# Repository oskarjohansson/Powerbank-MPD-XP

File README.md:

# Powerbank 4S
A powerbank to primarily use with MDP-XP Modular Power Supply. It can be found [here](https://www.welectron.com/Miniware-MDP-XP-Modular-Power-Supply). 

## Background 
One of the problems when using li-ion batteries is the charging, without a proper charger the cells wil be damages and probably start a fire. To remove these problems one solution would be a BMS with USB-C as a charging and discharging port. This doesn't exist yet, so someone has to make it. 

## Specification
- 4S high power Li-ion 
- Charge with USB-C
- Discharge with USB-C/DC jack

## Hardware core

> The following parts will be used as the main part of the project

* Charge controller from TI - [BQ25723RSNR](https://www.ti.com/lit/ds/symlink/bq25723.pdf?ts=1637573546478&ref_url=https%253A%252F%252Feu.mouser.com%252F)
* USB-C PD Interface from onsemi - [FUSB302B01MPX](https://www.mouser.se/datasheet/2/308/1/FUSB302B_D-2314121.pdf)
* MCU from Microchip - [ATSAMD21G18A](https://ww1.microchip.com/downloads/en/DeviceDoc/SAM-D21DA1-Family-Data-Sheet-DS40001882G.pdf)

# Schematic and PCB

## PCB

* TBD

## Schematic 

* TBD

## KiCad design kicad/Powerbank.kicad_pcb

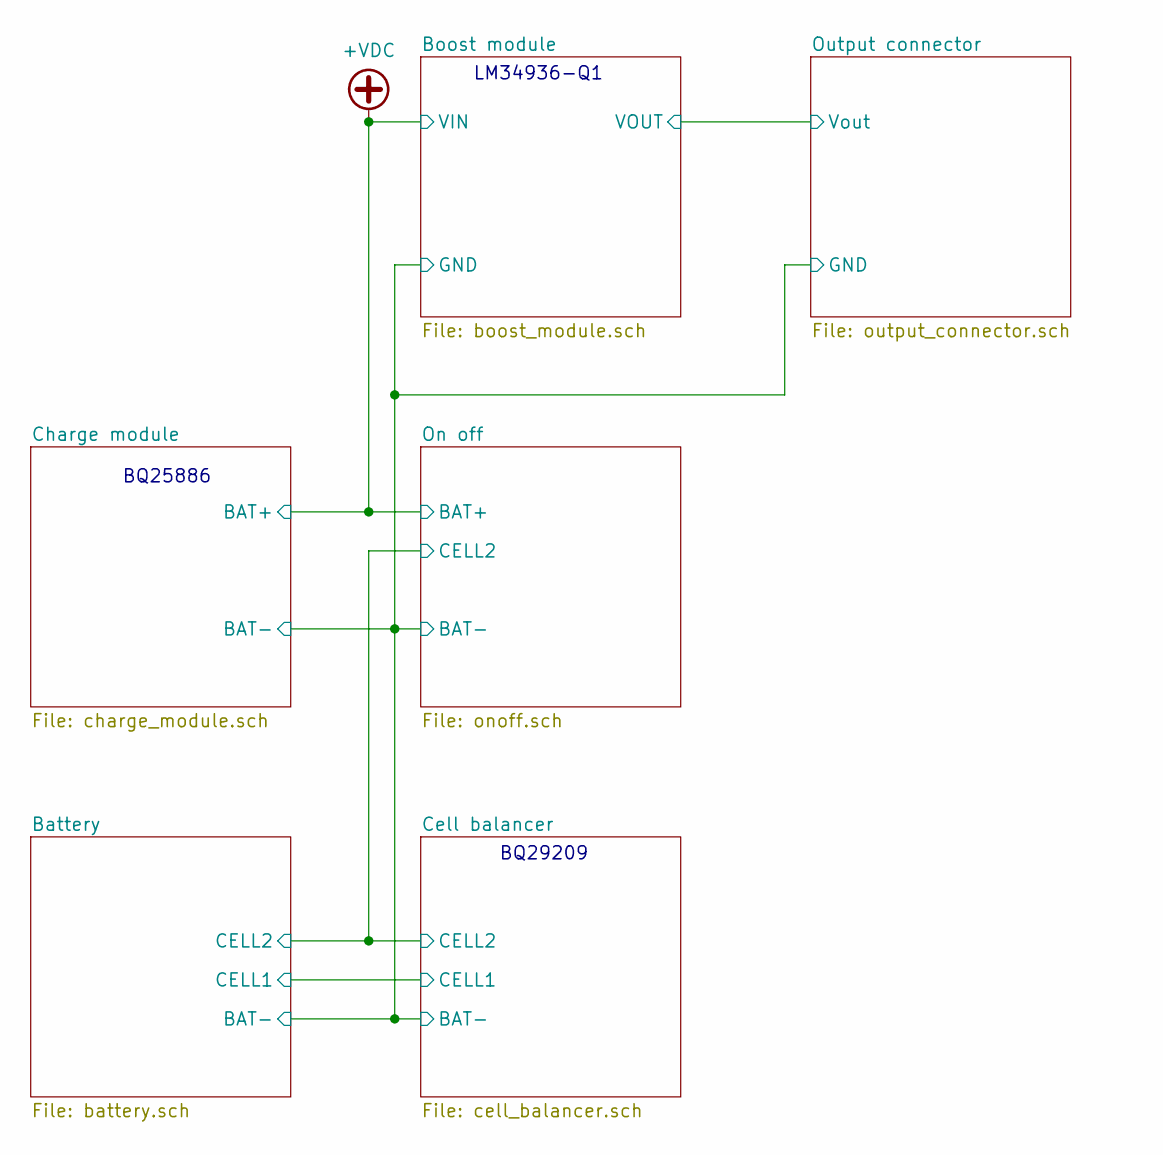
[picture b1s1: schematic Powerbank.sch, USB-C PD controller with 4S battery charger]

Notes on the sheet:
BQ25886
LM34936-Q1
BQ29209

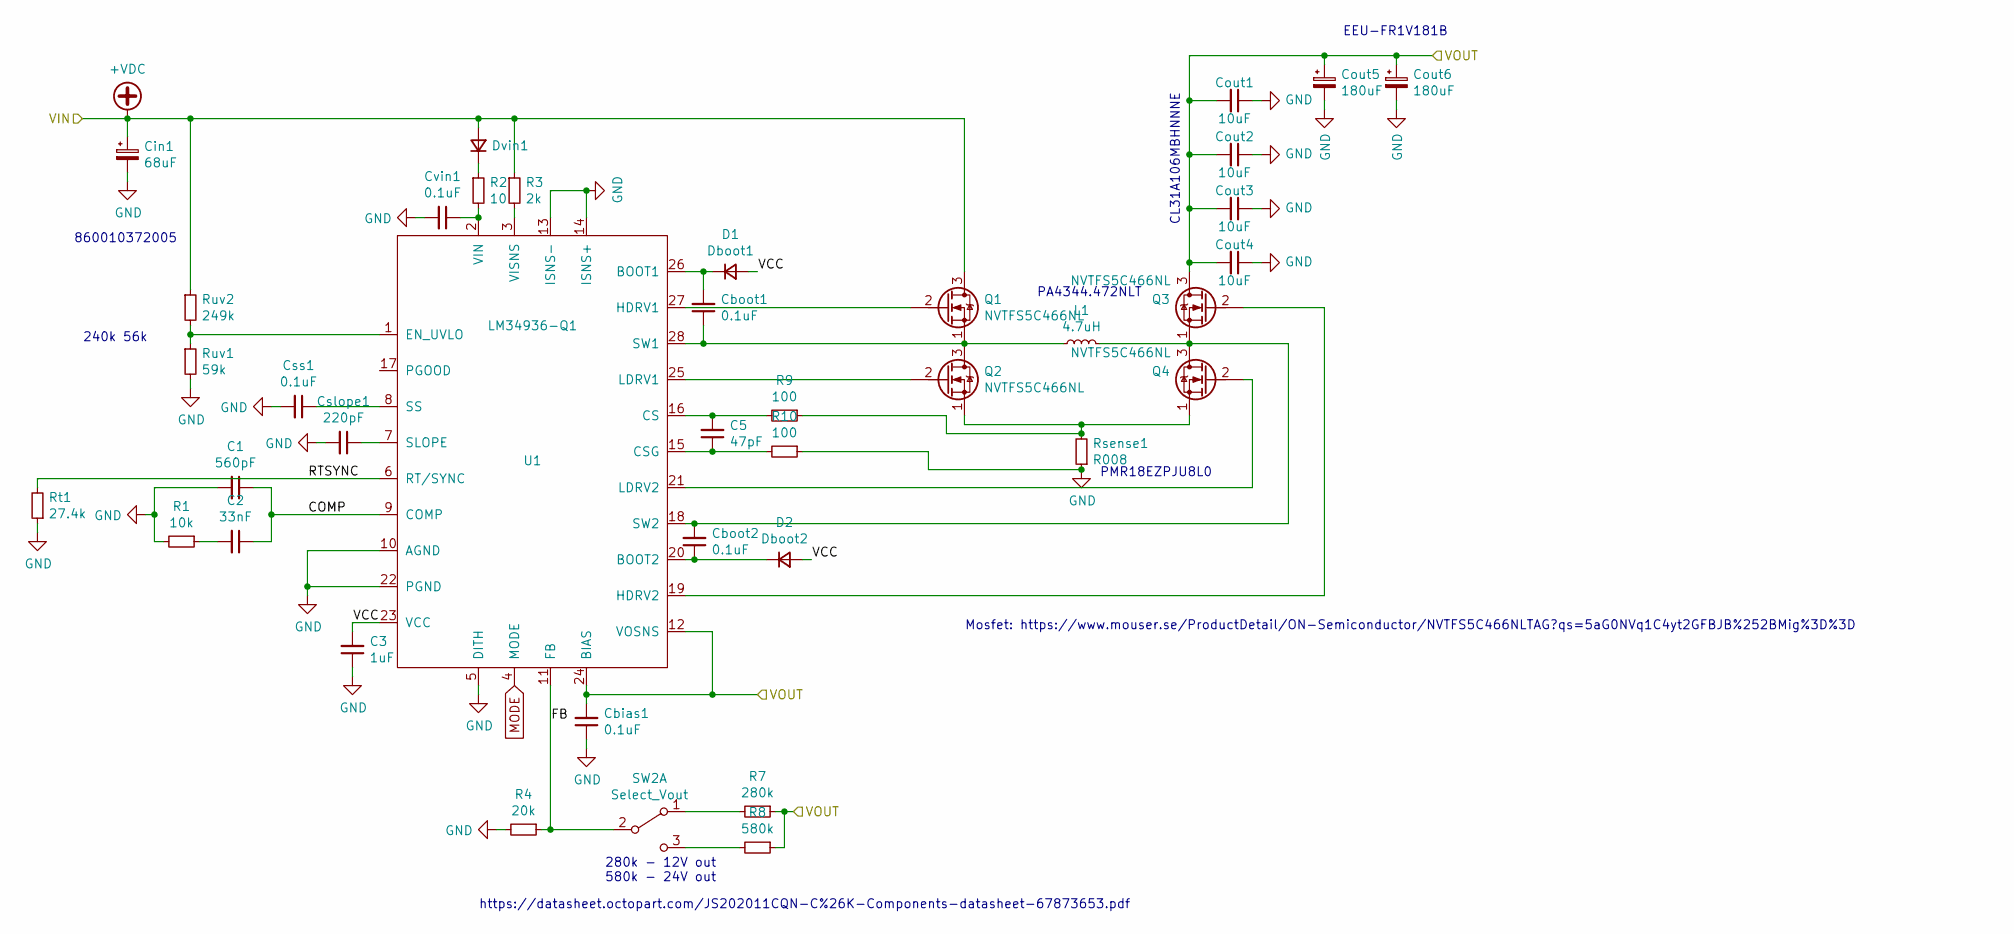
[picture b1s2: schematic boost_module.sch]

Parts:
C1: 560pF; C_0603_1608Metric
C2: 33nF; C_0603_1608Metric
C3: 1uF; C_0603_1608Metric
C5: 47pF; C_0603_1608Metric
Cbias1: 0.1uF; C_0603_1608Metric
Cboot1, Cboot2: 0.1uF; C_0603_1608Metric
Cin1: 68uF; CP_Radial_D5.0mm_P2.00mm
Cout1, Cout2, Cout3, Cout4: 10uF; C_1206_3216Metric
Cout5, Cout6: 180uF; CP_Radial_D8.0mm_P3.50mm
Cslope1: 220pF; C_0603_1608Metric
Css1: 0.1uF; C_0603_1608Metric
Cvin1: 0.1uF; C_0603_1608Metric
D1: Dboot1; D_SOD-123
D2: Dboot2; D_SOD-123
Dvin1: VIN; D_SOD-123
L1: 4.7uH; Pulse_PA4344.XXXNLT
Q1, Q2, Q3, Q4: NVTFS5C466NL; 8-PowerWDFN
R1: 10k; R_0603_1608Metric
R2: 10; R_0603_1608Metric
R3: 2k; R_0603_1608Metric
R4: 20k; R_0603_1608Metric
R7: 280k; R_0603_1608Metric
R8: 580k; R_0603_1608Metric
R9, R10: 100; R_0603_1608Metric
Rsense1: R008; R_1206_3216Metric
Rt1: 27.4k; R_0603_1608Metric
Ruv1: 59k; R_0603_1608Metric
Ruv2: 249k; R_0603_1608Metric
SW2: Select_Vout; JST_XH_B3B-XH-A_1x03_P2.50mm_Vertical
U1: LM34936-Q1; HTSSOP-28-1EP_4.4x9.7mm_P0.65mm_EP2.85x5.4mm_ThermalVias

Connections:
+VDC: Cin1.1, Dvin1.2 (A), Q1.3 (D), R3.1, Ruv2.1; also elsewhere on the board
/Boost module/COMP: C1.1, C2.1, U1.9 (COMP)
/Boost module/FB: R4.1, SW2.2 (B), U1.11 (FB)
/Boost module/RTSYNC: Rt1.2, U1.6 (RT/SYNC)
/Boost module/VCC: C3.2, D1.2 (A), D2.2 (A), U1.23 (VCC)
/Boost module/VOUT: Cbias1.2, Cout1.2, Cout2.2, Cout3.2, Cout4.2, Cout5.1, Cout6.1, Q3.3 (D), R7.1, R8.1, U1.12 (VOSNS), U1.24 (BIAS); also elsewhere on the board
GND: C1.2, C3.1, Cbias1.1, Cin1.2, Cout1.1, Cout2.1, Cout3.1, Cout4.1, Cout5.2, Cout6.2, Cslope1.2, Css1.2, Cvin1.2, R1.2, R4.2, R10.1, Rsense1.1, Rt1.1, Ruv1.2, U1.5 (DITH), U1.10 (AGND), U1.13 (ISNS-), U1.14 (ISNS+), U1.22 (PGND), U1.29 (PD); also elsewhere on the board
MODE: U1.4 (MODE)
unnamed: C2.2, R1.1
unnamed: C5.1, R10.2, U1.15 (CSG)
unnamed: C5.2, R9.2, U1.16 (CS)
unnamed: Cboot1.1, L1.1, Q1.1 (S), Q2.3 (D), U1.28 (SW1)
unnamed: Cboot1.2, D1.1 (K), U1.26 (BOOT1)
unnamed: Cboot2.1, D2.1 (K), U1.20 (BOOT2)
unnamed: Cboot2.2, L1.2, Q3.1 (S), Q4.3 (D), U1.18 (SW2)
unnamed: Cslope1.1, U1.7 (SLOPE)
unnamed: Css1.1, U1.8 (SS)
unnamed: Cvin1.1, R2.2, U1.2 (VIN)
unnamed: Dvin1.1 (K), R2.1
unnamed: Q1.2 (G), U1.27 (HDRV1)
unnamed: Q2.1 (S), Q4.1 (S), R9.1, Rsense1.2
unnamed: Q2.2 (G), U1.25 (LDRV1)
unnamed: Q3.2 (G), U1.19 (HDRV2)
unnamed: Q4.2 (G), U1.21 (LDRV2)
unnamed: R3.2, U1.3 (VISNS)
unnamed: R7.2, SW2.1 (A)
unnamed: R8.2, SW2.3 (C)
unnamed: Ruv1.1, Ruv2.2, U1.1 (EN_UVLO)

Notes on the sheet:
280k - 12V out 580k - 24V out
https://datasheet.octopart.com/JS202011CQN-C%26K-Components-datasheet-67873653.pdf
Mosfet: https://www.mouser.se/ProductDetail/ON-Semiconductor/NVTFS5C466NLTAG?qs=5aG0NVq1C4yt2GFBJB%252BMig%3D%3D
PMR18EZPJU8L0
PA4344.472NLT
EEU-FR1V181B
CL31A106MBHNNNE
860010372005
240k 56k

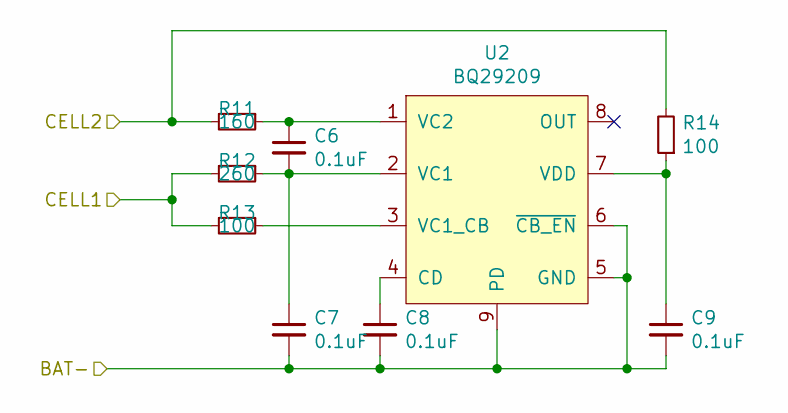
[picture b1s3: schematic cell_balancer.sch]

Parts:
C6, C7, C8, C9: 0.1uF; C_0603_1608Metric
R11: 160; R_0603_1608Metric
R12: 260; R_0603_1608Metric
R13, R14: 100; R_0603_1608Metric
U2: BQ29209; BQ29209DRBR

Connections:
/Battery/CELL1: R12.2, R13.2; also elsewhere on the board
/Battery/CELL2: R11.2, R14.2; also elsewhere on the board
GND: C7.2, C8.2, C9.2, U2.5 (GND), U2.6 (~CB_EN), U2.9 (PD); also elsewhere on the board
unnamed: C6.1, R11.1, U2.1 (VC2)
unnamed: C6.2, C7.1, R12.1, U2.2 (VC1)
unnamed: C8.1, U2.4 (CD)
unnamed: C9.1, R14.1, U2.7 (VDD)
unnamed: R13.1, U2.3 (VC1_CB)

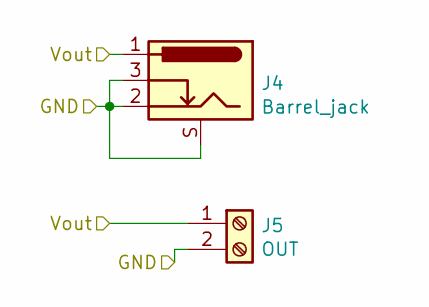
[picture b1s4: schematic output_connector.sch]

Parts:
J4: Barrel_jack; PJ079BH
J5: OUT; TerminalBlock_02_P5.00mm

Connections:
/Boost module/VOUT: J4.1, J5.1; also elsewhere on the board
GND: J4.2, J4.3, J4.S (Shield), J5.2; also elsewhere on the board

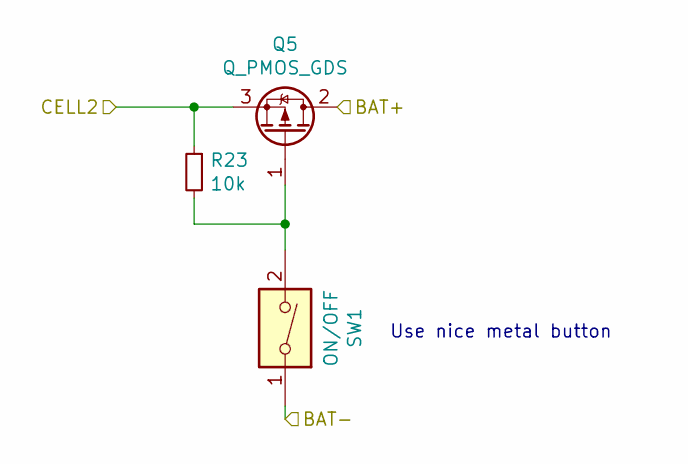
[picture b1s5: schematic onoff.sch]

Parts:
Q5: Q_PMOS_GDS; TO-252-2
R23: 10k; R_0603_1608Metric
SW1: ON/OFF; JST_XH_B2B-XH-A_1x02_P2.50mm_Vertical

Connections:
+VDC: Q5.2 (D); also elsewhere on the board
/Battery/CELL2: Q5.3 (S), R23.1; also elsewhere on the board
GND: SW1.1; also elsewhere on the board
unnamed: Q5.1 (G), R23.2, SW1.2

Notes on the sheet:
Use nice metal button

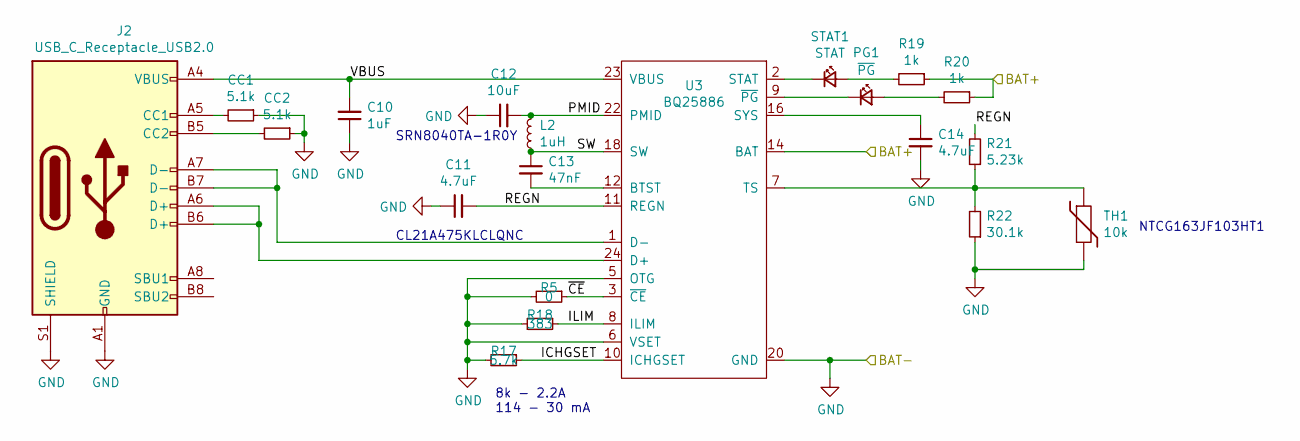
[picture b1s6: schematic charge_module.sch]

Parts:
C10: 1uF; C_0603_1608Metric
C11, C14: 4.7uF; C_0805_2012Metric
C12: 10uF; C_1206_3216Metric
C13: 47nF; C_0603_1608Metric
CC1, CC2: 5.1k; R_0603_1608Metric
J2: USB_C_Receptacle_USB2.0; USB_C_JAE_DX07S016JA1R1500
L2: 1uH; L_Bourns_SRN8040TA
PG1: ~PG; D_0603_1608Metric
R5: 0; R_0603_1608Metric
R17: 5.7k; R_0603_1608Metric
R18: 383; R_0603_1608Metric
R19, R20: 1k; R_0603_1608Metric
R21: 5.23k; R_0603_1608Metric
R22: 30.1k; R_0603_1608Metric
STAT1: STAT; D_0603_1608Metric
TH1: 10k; R_0603_1608Metric
U3: BQ25886; VQFN-24-1EP_4x4mm_P0.5mm_EP2.45x2.45mm_ThermalVias

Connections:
+VDC: R19.1, R20.1, U3.13 (BAT), U3.14 (BAT); also elsewhere on the board
/Charge module/ICHGSET: R17.1, U3.10 (ICHGSET)
/Charge module/ILIM: R18.1, U3.8 (ILIM)
/Charge module/PMID: C12.2, L2.2, U3.21 (PMID), U3.22 (PMID)
/Charge module/REGN: C11.2, R21.2, U3.11 (REGN)
/Charge module/SW: C13.1, L2.1, U3.17 (SW), U3.18 (SW)
/Charge module/VBUS: C10.2, J2.A4 (VBUS), J2.A9 (VBUS), J2.B4 (VBUS), J2.B9 (VBUS), U3.23 (VBUS)
/Charge module/~CE: R5.1, U3.3 (~CE)
GND: C10.1, C11.1, C12.1, C14.2, CC1.1, CC2.1, J2.A1 (GND), J2.A12 (GND), J2.B1 (GND), J2.B12 (GND), J2.S1 (SHIELD), R5.2, R17.2, R18.2, R22.1, TH1.2, U3.5 (OTG), U3.6 (VSET), U3.19 (GND), U3.20 (GND), U3.25 (PD); also elsewhere on the board
unnamed: C13.2, U3.12 (BTST)
unnamed: C14.1, U3.15 (SYS), U3.16 (SYS)
unnamed: CC1.2, J2.A5 (CC1)
unnamed: CC2.2, J2.B5 (CC2)
unnamed: J2.A6 (D+), J2.B6 (D+), U3.24 (D+)
unnamed: J2.A7 (D-), J2.B7 (D-), U3.1 (D-)
unnamed: PG1.1 (K), U3.9 (~PG)
unnamed: PG1.2 (A), R20.2
unnamed: R19.2, STAT1.2 (A)
unnamed: R21.1, R22.2, TH1.1, U3.7 (TS)
unnamed: STAT1.1 (K), U3.2 (STAT)

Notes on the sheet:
8k - 2.2A 114 - 30 mA
NTCG163JF103HT1
CL21A475KLCLQNC
SRN8040TA-1R0Y

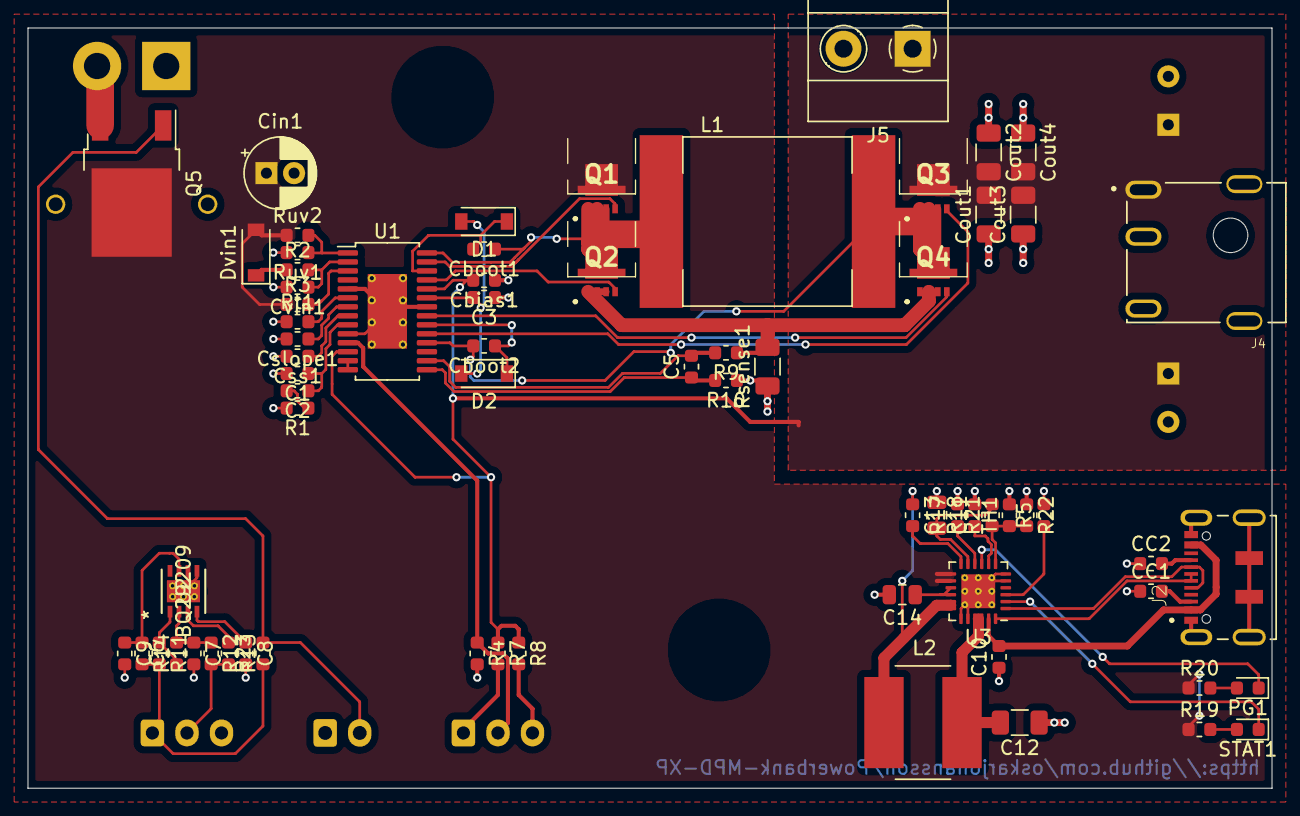
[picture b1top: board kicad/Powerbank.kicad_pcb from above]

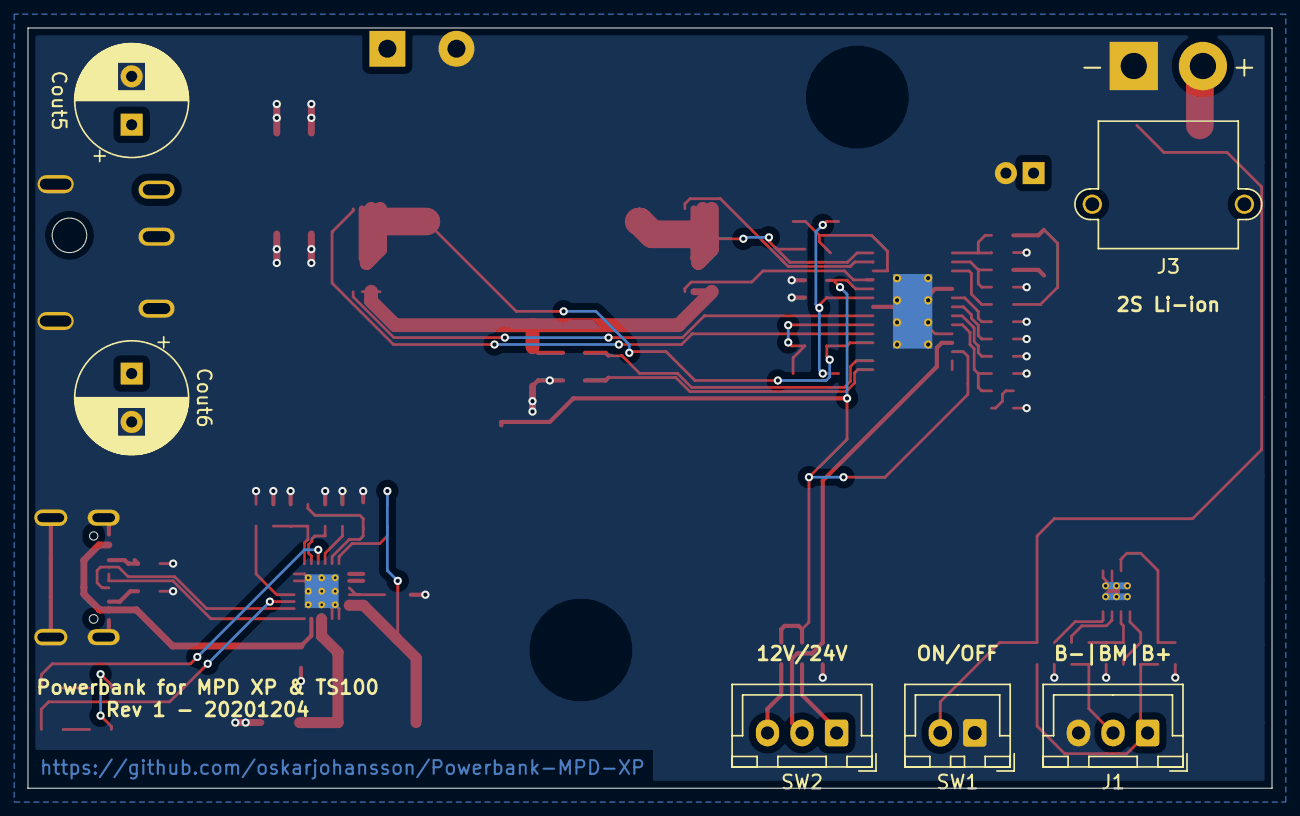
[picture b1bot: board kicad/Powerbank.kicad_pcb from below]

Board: 2 copper layers, 90.0 x 55.0 mm, 75 parts (6 on the bottom side), 53 nets.

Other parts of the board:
J1: Balance conn; JST_XH_B3B-XH-A_1x03_P2.50mm_Vertical
J3: Bat conn; XT30PW-M

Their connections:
/Battery/CELL1: J1.2; also elsewhere on the board
/Battery/CELL2: J1.1, J3.2; also elsewhere on the board
GND: J1.3, J3.1; also elsewhere on the board

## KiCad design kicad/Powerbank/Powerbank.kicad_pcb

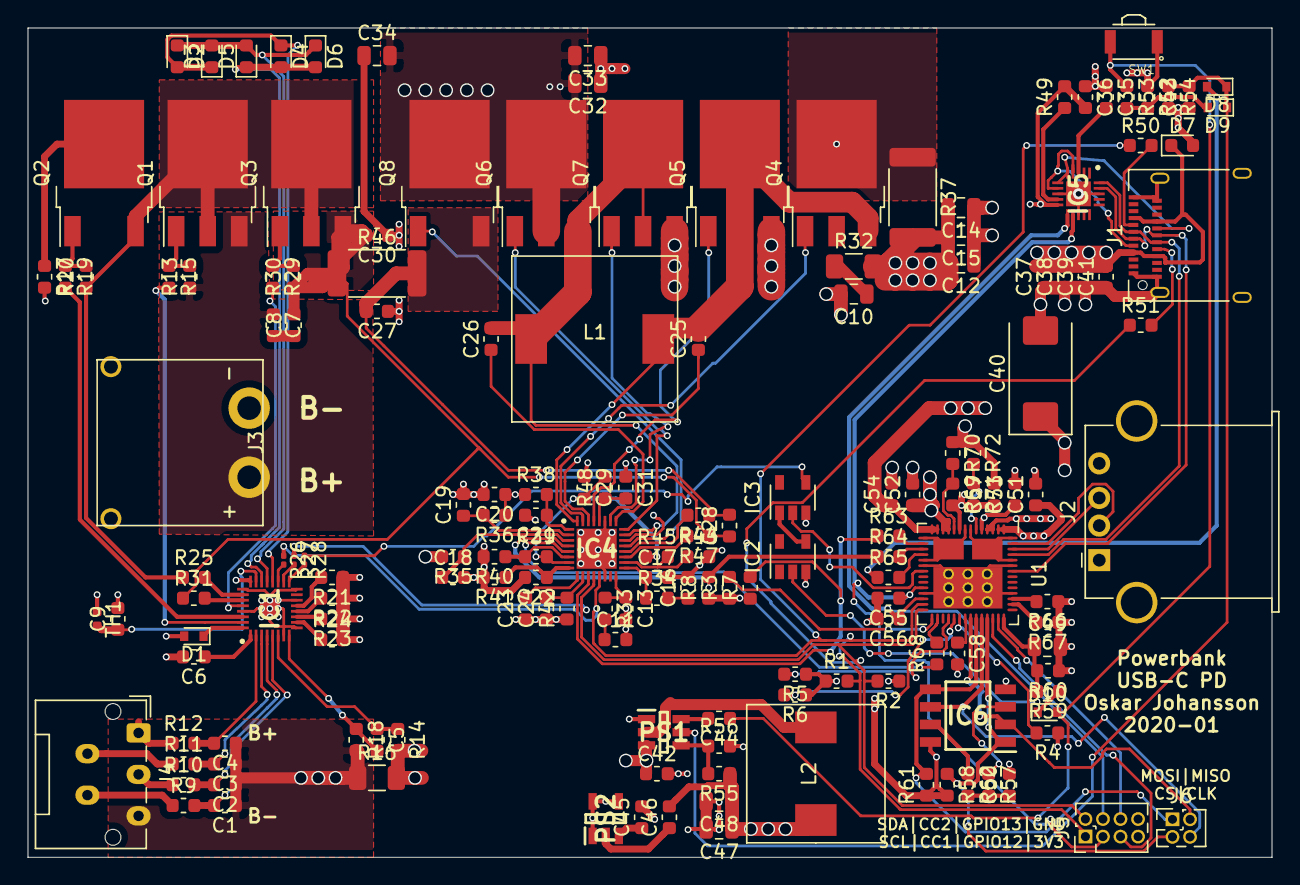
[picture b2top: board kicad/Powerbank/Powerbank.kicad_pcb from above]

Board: 4 copper layers, 90.0 x 60.0 mm, 167 parts (0 on the bottom side), 127 nets.

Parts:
C1, C2, C3, C4, C5, C7, C9, C28, C35, C44, C46, C50: 0.1µF; C_0603_1608Metric
C6, C31: 2.2µF; C_0603_1608Metric
C8: 0.22µF; C_0603_1608Metric
C10, C12, C14, C15, C32, C33, C34, C47, C48, C49: 22µF; C_0805_2012Metric
C11: 1800pF; C_0603_1608Metric
C13: 33pF; C_0603_1608Metric
C16: 680pF; C_0603_1608Metric
C17: 15pF; C_0603_1608Metric
C18, C19: 0.033µF; C_0603_1608Metric
C20, C37, C38, C39, C41: 0.01µF; C_0603_1608Metric
C21: 0.47µF; C_0603_1608Metric
C22, C23, C24: 100pF; C_0603_1608Metric
C25, C26: 0.047µF; C_0603_1608Metric
C27, C29, C36, C45, C54: 1µF; C_0603_1608Metric
C30, C42, C43, C51, C52, C53, C57: 10µF; C_0603_1608Metric
C40: 100µF; CP_EIA-7343-15_Kemet-W
C55, C56: 330pF; C_0603_1608Metric
C58: 4.7µF; C_0603_1608Metric
D1, D8, D9, D10: D_Schottky; D_SOD-523
D2, D3, D4, D5, D6: LED; LED_0603_1608Metric
D7: D_Schottky; D_0603_1608Metric
IC1: BQ4050RSMR; QFN40P400X400X100-33N-D
IC2: SN74LVC1G14DSFR; SOT-23-5
IC3: SN74LVC1G08DSFR; SOT-23-5
IC4: BQ25703ARSNT; QFN40P400X400X80-33N-D
IC5: TPD6S300ARUKR; QFN40P300X300X80-21N-D
IC6: W25Q80DVSNIG; SOIC127P600X175-8N
J1: USB_C_Receptacle; USB_C_Receptacle_Amphenol_12401610E4-2A
J2: USB_A; USB_A_Stewart_SS-52100-001_Horizontal
J3: Conn_01x02_Male; XT30PW-M
J4: Conn_01x05_Male; JST_ZE_S05B-ZESK-2D_1x05_P1.50mm_Horizontal
J5: Conn_01x08_Male; PinHeader_2x04_P1.27mm_Vertical
J6: Conn_01x04_Male; PinHeader_2x02_P1.27mm_Vertical
L1: 2.2µH; WE_Inductor_7443330220
L2: 3.3µH; WE_Inductor_8070_7443340330
PS1: TPS563200DDCT; SOT95P280X110-6N
PS2: TLV70433DBVR; SOT95P280X145-5N
Q1, Q3, Q4, Q5, Q6, Q7: Q_NMOS_GDS; TO-252-3_TabPin2
Q2, Q8: Q_PMOS_GDS; TO-252-2
R1, R2, R5, R6, R7, R8: 3.83k; R_0603_1608Metric
R3, R4, R21, R22, R23, R24, R31, R34, R56, R71: 10k; R_0603_1608Metric
R9, R10, R11, R12, R25: 100R; R_0603_1608Metric
R13, R20, R30: 10M; R_0603_1608Metric
R14, R18: 100; R_0603_1608Metric
R15, R19, R29: 5.1k; R_0603_1608Metric
R16: 0.001; R_1206_3216Metric
R17: 300; R_0603_1608Metric
R26, R27, R28: DNP; R_0201_0603Metric
R32: 2.2R; R_1206_3216Metric
R33: 40.2k; R_0603_1608Metric
R35, R36: 4.99R; R_0603_1608Metric
R37, R46: 0.01R; R_2512_6332Metric
R38: 1R; R_0603_1608Metric
R39, R40: 100K; R_0603_1608Metric
R41: 137k; R_0603_1608Metric
R42: 30k; R_0603_1608Metric
R43, R49, R54, R60, R67, R69, R70, R72: 100k; R_0603_1608Metric
R44, R47, R48: 10R; R_0603_1608Metric
R45: 35k; R_0603_1608Metric
R50, R51: DNP; R_0603_1608Metric
R52, R53, R59: 270k; R_0603_1608Metric
R55: 54.9k; R_0603_1608Metric
R57, R58, R61, R62: 3.3k; R_0603_1608Metric
R63, R64, R65, R68: 0; R_0603_1608Metric
R66: 5.10k; R_0603_1608Metric
SW1: SW_DIP_x01; SW_B3U-3000P
TH1: 10k; R_0402_1005Metric
U1: TPS65988DH; QFN-56_7x7_Pitch0.4mm

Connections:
+3V3: C45.2, C53.1, J5.7, U1.5
+5V: C46.2, C47.1, C48.1, C51.1, L2.2, R55.1, U1.1, U1.2
+VDC: C8.2, C28.1, C30.2, Q3.3, R30.1, R31.1, R46.1, R47.1
-BATT: C1.1, C2.1, C3.1, C4.1, C6.2, IC1.7, IC1.9, IC1.14, IC1.16, IC1.25, IC1.29, IC1.33, J3.2, J4.5, R16.1, R18.2, R21.1, R22.1, R23.1, R24.2
/Cell Balancer BQ4050/Source: Q1.2, Q2.3, Q3.2, R20.1, R25.1
ACN: C19.1, IC4.2, R36.2
ACP: C18.1, IC4.3, R35.1
ADCIN1: R71.1, R72.2, U1.6
ADCIN2: R69.1, R70.2, U1.10
CC1: C55.1, IC5.12, J5.3, U1.24
CC1_CONN: IC5.4, IC5.7, J1.A5
CC2: C56.1, IC5.11, J5.4, U1.26
CC2_CONN: IC5.5, IC5.6, J1.B5
CELL1: J4.4, R9.1
CELL2: J4.3, R10.1
CELL3: J4.2, R11.1
CELL4: C7.1, C9.2, D1.2, IC1.24, J3.1, J4.1, Q1.3, R12.1, R13.1, R17.2, TH1.1
CHRG_OK: IC4.4, R8.2, R64.1
COMP1: C13.1, IC4.16, R33.1
COMP2: C17.1, IC4.17, R34.1
DISP: IC3.4, R28.1
DN_A: J2.2, U1.55
DN_C: IC5.20, J1.A7, J1.B7, U1.53
DP_A: J2.3, U1.54
DP_C: IC5.19, J1.A6, J1.B6, U1.50
DRAIN1: U1.8, U1.15, U1.19, U1.58
DRAIN2: U1.7, U1.52, U1.56, U1.57
EN_OTG: IC4.5, R68.1
GND: C10.2, C11.2, C12.1, C13.2, C14.1, C15.1, C16.2, C17.2, C18.2, C19.2, C20.2, C21.2, C22.2, C23.1, C24.1, C27.1, C29.1, C30.1, C31.1, C32.1, C33.1, C34.1, C35.1, C36.1, C37.1, C38.1, C39.1, C40.2, C41.1, C42.2, C43.1, C47.2, C48.2, C49.2, C50.2, C51.2, C52.2, C53.2, C54.2, C55.2, C56.2, C57.2, C58.2, D7.2, IC2.3, IC3.3, IC4.14, IC4.27, IC4.33, IC5.8, IC5.13, IC5.18, IC5.21, IC6.4, J1.A1, J1.A12, J1.B1, J1.B12, J1.S1, J2.4, J2.5, J5.8, PS1.1, PS2.1, PS2.4, PS2.5, Q5.3, Q7.3, R14.2, R16.2, R40.2, R41.2, R42.1, R43.2, R54.2, R56.2, R60.1, R66.1, R67.1, R70.1, R72.1, U1.20, U1.25, U1.46, U1.51, U1.59
GPIO12: J5.5, U1.40
GPIO13: J5.6, U1.41
IRQ_1: R3.2, U1.29
IRQ_2: R4.2, U1.34
LDO_1V8: C58.1, U1.35
unnamed: C1.2, IC1.5, R9.2
unnamed: C2.2, IC1.4, R10.2
unnamed: C3.2, IC1.3, R11.2
unnamed: C4.2, IC1.2, R12.2
unnamed: C5.1, IC1.6, R14.1
unnamed: C5.2, IC1.8, R18.1
unnamed: C6.1, IC1.1
unnamed: C7.2, C8.1
unnamed: C9.1, IC1.23, TH1.2
unnamed: C10.1, R32.1
unnamed: C11.1, R33.2
unnamed: C16.1, R34.2
unnamed: C20.1, Q4.2, R36.1, R37.1, R38.1
unnamed: C21.1, IC4.1, R38.2
unnamed: C22.1, IC4.8, R41.1
unnamed: C23.2, IC4.9
unnamed: C24.2, IC4.10, R42.2
unnamed: C25.1, IC4.30
unnamed: C26.1, IC4.25
unnamed: C27.2, C28.2, Q8.3, R44.1, R46.2
unnamed: C35.2, IC5.3
unnamed: C44.2, PS1.6
unnamed: C45.1, PS2.3
unnamed: C46.1, PS2.2
unnamed: C50.1, R57.2, R62.2
unnamed: D1.1, IC1.32
unnamed: D2.1, D3.2, D5.2, D6.1, IC1.21
unnamed: D2.2, D3.1, D4.1, IC1.20
unnamed: D4.2, D5.1, D6.2, IC1.22
unnamed: D9.2, R52.2, R53.2
unnamed: D10.1, R59.1
unnamed: IC1.10, R24.1
unnamed: IC1.11, R23.2
unnamed: IC1.12, R22.2
unnamed: IC1.13, R21.2
unnamed: IC1.17, R28.2
unnamed: IC1.18, R27.2
unnamed: IC1.19, R26.2
unnamed: IC1.26, R25.2
unnamed: IC1.27, R31.2
unnamed: IC1.28, R29.2
unnamed: IC1.30, R19.2
unnamed: IC1.31, R15.2
unnamed: IC2.4, IC3.1
unnamed: IC4.6, R39.1, R40.1
unnamed: IC4.18, R43.1, R45.2
unnamed: IC4.19, R47.2
unnamed: IC4.20, R44.2
unnamed: IC4.21, Q8.1
unnamed: IC5.9, R49.1
unnamed: IC6.3, R57.1
unnamed: IC6.7, R62.1
unnamed: J1.A8, R50.2
unnamed: J1.B8, R51.2
unnamed: L2.1, PS1.2
unnamed: PS1.4, R55.2, R56.1
unnamed: Q1.1, R13.2, R15.1
unnamed: Q2.1, R19.1, R20.2
unnamed: Q2.2, R17.1
unnamed: Q3.1, R29.1, R30.2
unnamed: R63.2, U1.16
unnamed: R64.2, U1.17
unnamed: R65.2, U1.18
unnamed: R66.2, U1.45
unnamed: R67.2, U1.44
unnamed: R68.2, U1.30
PD_LDO_3V3: C36.2, C57.1, IC5.10, IC6.8, R1.1, R2.1, R3.1, R4.1, R5.1, R6.1, R7.1, R8.1, R49.2, R58.2, R61.1, R69.2, R71.2, U1.9
PP_HV: C12.2, C14.2, C15.2, C52.1, R32.2, R35.2, R37.2, U1.11, U1.12
PROCHOT: IC4.11, R7.2, R63.1
REGN: C31.2, IC4.28, R48.1
SCL_1: IC4.13, J5.1, R1.2, R26.1, R50.1, U1.27
SCL_2: R5.2, U1.32
SDA_1: IC4.12, J5.2, R2.2, R27.1, R51.1, U1.28
SDA_2: R6.2, U1.33
SNK_EVENT: IC3.2, U1.21
SPI_CLK: IC6.6, J6.4, U1.38
SPI_CSZ: IC6.1, J6.3, R58.1, U1.39
SPI_MISO: IC6.2, J6.2, U1.36
SPI_MOSI: IC6.5, J6.1, R61.2, U1.37
SRC_EVT: D8.2, R65.1
SW: C44.1, D10.2, R53.1, SW1.2
SW_SIG: C49.1, IC2.2, R59.2, R60.2, U1.42
SYS: C32.2, C33.2, C34.2, C42.1, IC4.22, PS1.3, Q6.2, Q8.2, R52.1, SW1.1
SYS_EN: C43.2, D8.1, D9.1, PS1.5, R54.1
TP1: C25.2, IC4.32, L1.1, Q4.3, Q5.2
TP2: C26.2, IC4.23, L1.2, Q6.3, Q7.2
TP3: IC4.29, Q5.1
TP4: IC4.26, Q7.1
TP5: IC4.31, Q4.1
TP6: IC4.24, Q6.1
VBUS_A: C40.1, J2.1, U1.3, U1.4
VBUS_C: C37.2, C38.2, C39.2, C41.2, C54.1, D7.1, J1.A4, J1.A9, J1.B4, J1.B9, U1.13, U1.14
VDDA: C29.2, IC4.7, R39.2, R45.1, R48.2

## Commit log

2019-10-15 Initial commit
    Just setup everything in eagle and a gitignore file.
2020-01-01 Added TI reference design
2020-01-01 Switched to KiCAD instead of Eagle
2020-01-01 Added project library and cell balancer schematic
2020-01-01 Added sheet for cell balancer
2020-01-01 Added more schematics and battery + balancer
2020-01-01 Added more schematics
2020-01-02 Completed cell balancer according to ref schematic
    [found here](]http://www.ti.com/lit/df/tidrzn1/tidrzn1.pdf)
2020-01-02 Battery charger completed according to reference guide
2020-01-02 Completed buck according to reference guide
2020-01-02 Added USB C + A and protection circuit according to ref. design
2020-01-02 Added PD Controller according to reference design
2020-01-02 Moved LDO to Buck sheet and started check of components
2020-01-02 Double checked schematic towards reference design
2020-01-02 Ignore schematic backup files
2020-01-02 Added footprint and 3D model
2020-01-02 Updated for PCB
2020-01-02 Added datasheets
2020-01-02 Assigned inductor with footprint
2020-01-02 Updated PCB
2020-01-02 Ignore PCB backup
2020-01-03 Added footprint for all, moved to a first attempt for routing
2020-01-03 Added more routing
2020-01-04 Routed some of components of battery charger
2020-01-04 Changed to 0805 on 22uF capacitor
2020-01-04 Updated routing
2020-01-07 First routing finished, correcting DRC warnings
2020-01-07 DRC almost finished and added cap for USB-A
2020-01-08 Double checked footprint for IC and Mosfets
2020-01-11 Updated layout in schematic for nicer look
2020-01-11 Exported schematics
2020-01-11 Renamed without spaces
2020-01-11 Added schematic
2020-01-11 Added image of PCB
2020-01-11 Create BOM and exported cart from Digikey with all components
    The cart includes multiples of different components due to cheaper.
2020-11-23 Datasheet for boost and charge chip
2020-11-23 Updated to match the new project
2020-11-24 Removed and moved files
2020-11-24 New design, only powerbank for mpd
2020-11-24 New names
2021-01-14 Updated schematic
    Made some error with first rev, the found error are now corrected.
2021-01-14 Exported gerber files for rev 1
2021-01-14 Export interactive BOM
2021-01-14 Added datasheet
2021-01-14 Exported PCB for rev 1
2021-01-14 CAD for enclosure
2021-08-05 Remove first design
2021-08-05 Initial commit for new design
2021-09-27 Added USB PD and charge circuits
    Only added a simple symbol for the ordererd components. Now I have to go on with these and hopefully they will work.
2021-11-22 Reinitialise project
    The project was paused after I found out
    that the power supply does not support
    USB PD, only QC. But with a new idea the
    project will be continued.
2021-12-02 Added buck boost charger
2021-12-11 Add processor and PD controller
    Just trying to create a first schematic over the pieces in the project.
2021-12-11 Update kicadlib

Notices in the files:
parts and their libraries:
Copyright 2016 Accelerated Designs. All rights reserved.
